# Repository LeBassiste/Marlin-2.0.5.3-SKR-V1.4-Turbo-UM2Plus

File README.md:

# Marlin-2.0.5.3-SKR-V1.4-Turbo-UM2Plus
Marlin 2.0.5.3 Settings for BIGTREE SKR 1.4_Turbo, TMC5160 to drive Ultimaker UM2+ 3D Printer
version V2 contains updated and sanitized header files to reflect changes in
configuration.h
configuration_adv.h
pins_BT_SKR_c ommon.h
search for "habe" to find all modifications

reduced spill when preloading hotend before print.
increased motor currents to 800 mA and 32 microsteps to improve wall smoothness.

1.Required Hardware					
  a.  1	 BTT SKR 1.4 Turbo				
  b.  4	TMC5160 Stepper drivers				
  c.  1	BTT DCDC Power Module for SKR 1.4				
  d.  1	 PT100 Pre-Amplifier (Ultimaker Style), 3 channel, must use VDD = 3.3 VDC (DIY), see KICAD file	SKR14_PT100_Amp		
  e.  1	MOSFET Adapter Board to run Hotend Fan off of SERVO connector (DIY), see KICAD file SKR14_FAN_DRIVE				

2. What will these Mods do?					
	a.  Enable flicker-free dimmable Case Lighting, using the original Ultimaker Case LEDs @ 24 VDC and high frequency PWM dimming		
	b.  enable PWM-controlled Parts Fan				
	c.  enable PWM-controlled 5VDC for use with Hotend Fan	(needs extra MOSFET and Diode, driven from SERVO connector)			
	d.  increase Bed-Heater and Hotend-Heater PWM to 60 Hz to smoothen power consumption (note: you must use PID for Bed Heater). 
      This improves print quality!				
	e.  enable ulticontroller display and Clickwheel+LEDs as published by Anthrix https://community.ultimaker.com/topic/30786-ultimaker-with-skr-14/

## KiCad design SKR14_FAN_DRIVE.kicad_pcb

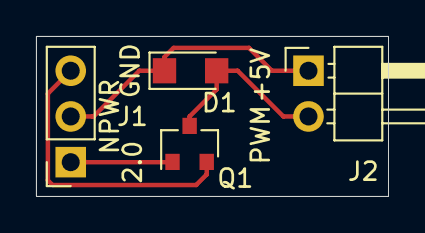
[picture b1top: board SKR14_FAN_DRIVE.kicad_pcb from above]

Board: 2 copper layers, 19.6 x 8.9 mm, 4 parts (0 on the bottom side), 4 nets.

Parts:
D1: SL03-M-08; D_SMF
J1: Conn_01x03_Female; PinSocket_1x03_P2.54mm_Vertical
J2: Conn_01x02_Male; PinHeader_1x02_P2.54mm_Horizontal
Q1: 2N7002P; SOT-23

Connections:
/GND: J1.3, Q1.2
/NPWR: D1.1, J1.2, J2.1
/P2_00: J1.1, Q1.1
unnamed: D1.2, J2.2, Q1.3

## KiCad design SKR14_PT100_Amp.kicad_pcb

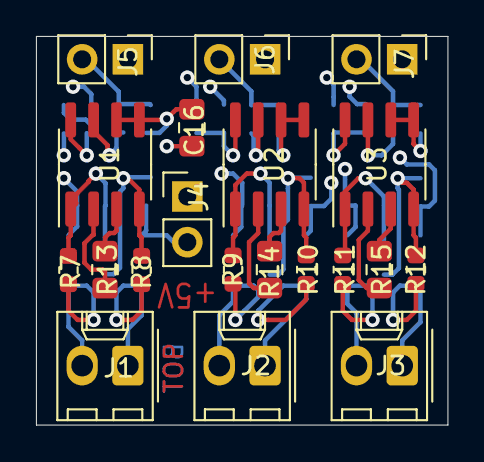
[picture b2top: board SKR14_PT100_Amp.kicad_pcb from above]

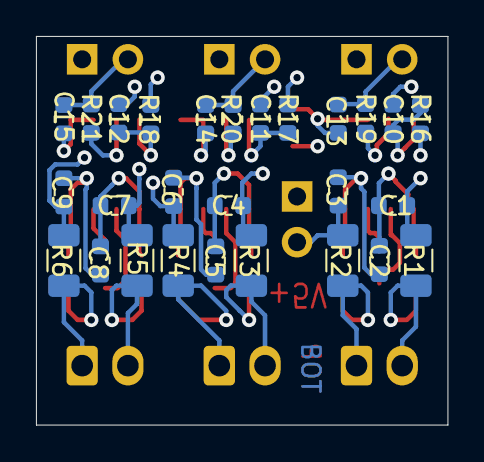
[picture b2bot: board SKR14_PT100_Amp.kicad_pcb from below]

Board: 4 copper layers, 22.9 x 21.6 mm, 47 parts (27 on the bottom side), 29 nets.

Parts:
C1, C2, C3, C4, C5, C6, C7, C8, C9, C10, C11, C12: 100nF; C_0603_1608Metric
C13, C14, C15: dnp; C_0603_1608Metric
C16: 10uF / 25V; C_0805_2012Metric_Pad1.15x1.40mm_HandSolder
J1, J2, J3: Conn_01x02_Male; Molex_KK-254_AE-6410-02A_1x02_P2.54mm_Vertical
J4, J5, J6, J7: Conn_01x02_Male; PinHeader_1x02_P2.54mm_Vertical
R1, R2, R3, R4, R5, R6: 2k2; R_1206_3216Metric
R7, R8, R9, R10, R11, R12: 10k; R_0603_1608Metric
R13, R14, R15: 5k49; R_0805_2012Metric_Pad1.15x1.40mm_HandSolder
R16, R17, R18, R19, R20, R21: 100; R_0603_1608Metric
U1, U2, U3: INA826; SOIC-8_3.9x4.9mm_P1.27mm

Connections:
+5V: C3.1, C6.1, C9.1, C16.2, J4.2, R2.2, R4.2, R6.2, R16.1, R17.1, R18.1
GND: C1.2, C4.2, C7.2, C10.1, C11.1, C12.1, C13.2, C14.2, C15.2, C16.1, J4.1, J5.1, J6.1, J7.1, R1.1, R3.1, R5.1, U1.5, U1.6, U2.5, U2.6, U3.5, U3.6
unnamed: C1.1, C2.2, R7.1, U1.1
unnamed: C2.1, C3.2, R8.1, U1.4
unnamed: C4.1, C5.2, R9.1, U2.1
unnamed: C5.1, C6.2, R10.1, U2.4
unnamed: C7.1, C8.2, R11.1, U3.1
unnamed: C8.1, C9.2, R12.1, U3.4
unnamed: C10.2, R16.2, U1.8
unnamed: C11.2, R17.2, U2.8
unnamed: C12.2, R18.2, U3.8
unnamed: C13.1, J5.2, R19.1
unnamed: C14.1, J6.2, R20.1
unnamed: C15.1, J7.2, R21.1
unnamed: J1.1, R2.1, R8.2
unnamed: J1.2, R1.2, R7.2
unnamed: J2.1, R4.1, R10.2
unnamed: J2.2, R3.2, R9.2
unnamed: J3.1, R6.1, R12.2
unnamed: J3.2, R5.2, R11.2
unnamed: R13.1, U1.2
unnamed: R13.2, U1.3
unnamed: R14.1, U2.2
unnamed: R14.2, U2.3
unnamed: R15.1, U3.2
unnamed: R15.2, U3.3
unnamed: R19.2, U1.7
unnamed: R20.2, U2.7
unnamed: R21.2, U3.7

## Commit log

2020-07-05 Add files via upload
    updated:
    configuration.h
    configuration_adv.h
    pins_BTT_SKR_common.h
2020-07-05 Delete Marlin-2.0.5.3-SKR1.4T_UM2plus.zip
    deleted for version V2 with sanitized header files. search for "habe" to find all changes.
2020-07-06 Add files via upload
    BOM for PT100_Amp, including Digikey order numbers.
